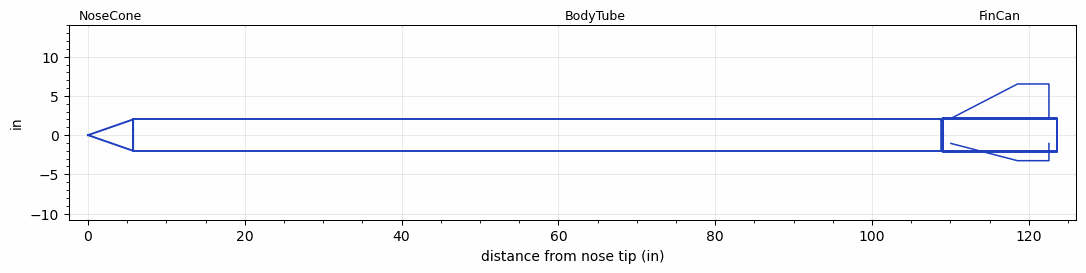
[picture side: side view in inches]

<RASAeroDocument>
 <FileVersion>2</FileVersion>
 <RocketDesign>
  <NoseCone>
   <Length>5.75</Length>
   <Diameter>4</Diameter>
   <Shape>Conical</Shape>
   <Location>0</Location>
  </NoseCone>
  <BodyTube>
   <Length>117.8125</Length>
   <Diameter>4</Diameter>
   <Location>5.75</Location>
  </BodyTube>
  <FinCan>
   <Length>14.5</Length>
   <Diameter>4.25</Diameter>
   <InsideDiameter>4</InsideDiameter>
   <Location>123.5625</Location>
   <ShoulderLength>0.2415</ShoulderLength>
   <Offset>-14.5</Offset>
   <Fin>
    <Count>3</Count>
    <Chord>12.5</Chord>
    <Span>4.4</Span>
    <SweepDistance>8.5</SweepDistance>
    <TipChord>4</TipChord>
    <Thickness>0.125</Thickness>
    <Location>13.5</Location>
    <AirfoilSection>Hexagonal</AirfoilSection>
    <FX1>0.25</FX1>
    <FX3>0.125</FX3>
   </Fin>
  </FinCan>
  <Surface>Smooth (Zero Roughness)</Surface>
  <ModifiedBarrowman>False</ModifiedBarrowman>
  <Turbulence>False</Turbulence>
  <SustainerNozzle>2.5</SustainerNozzle>
  <UseBooster1>False</UseBooster1>
  <UseBooster2>False</UseBooster2>
  <Comments>Full Metal Jacket - Black Rock 6
O10000 Motor
Frank Kosdon
Black Rock Launch Site

Optical Track
Altitude = 30038 ft

RASAero II Prediction = 32548 ft
Error = 8.36%
</Comments>
 </RocketDesign>
 <LaunchSite>
  <Altitude>3933</Altitude>
  <Pressure>0</Pressure>
  <RodAngle>0</RodAngle>
  <RodLength>12</RodLength>
  <Temperature>80</Temperature>
  <WindSpeed>0</WindSpeed>
 </LaunchSite>
 <Recovery>
  <Altitude1>1000</Altitude1>
  <Altitude2>1000</Altitude2>
  <DeviceType1>Parachute</DeviceType1>
  <DeviceType2>None</DeviceType2>
  <Event1>False</Event1>
  <Event2>False</Event2>
  <Size1>36</Size1>
  <Size2>1</Size2>
  <EventType1>Apogee</EventType1>
  <EventType2>None</EventType2>
  <CD1>1.33</CD1>
  <CD2>1.33</CD2>
 </Recovery>
 <SimulationList>
  <Simulation>
   <SustainerEngine>O10000  (Hist)</SustainerEngine>
   <SustainerLaunchWt>65</SustainerLaunchWt>
   <SustainerNozzleDiameter>2.5</SustainerNozzleDiameter>
   <SustainerCG>85</SustainerCG>
   <SustainerIgnitionDelay>0</SustainerIgnitionDelay>
   <Booster1SeparationDelay>0</Booster1SeparationDelay>
   <Booster1IgnitionDelay>0</Booster1IgnitionDelay>
   <IncludeBooster1>False</IncludeBooster1>
   <Booster2Delay>0</Booster2Delay>
   <IncludeBooster2>False</IncludeBooster2>
   <TimetoApogee>40.38923</TimetoApogee>
   <MaxAltitude>32547.94</MaxAltitude>
   <MaxVelocity>2743.863</MaxVelocity>
  </Simulation>
 </SimulationList>
</RASAeroDocument>
